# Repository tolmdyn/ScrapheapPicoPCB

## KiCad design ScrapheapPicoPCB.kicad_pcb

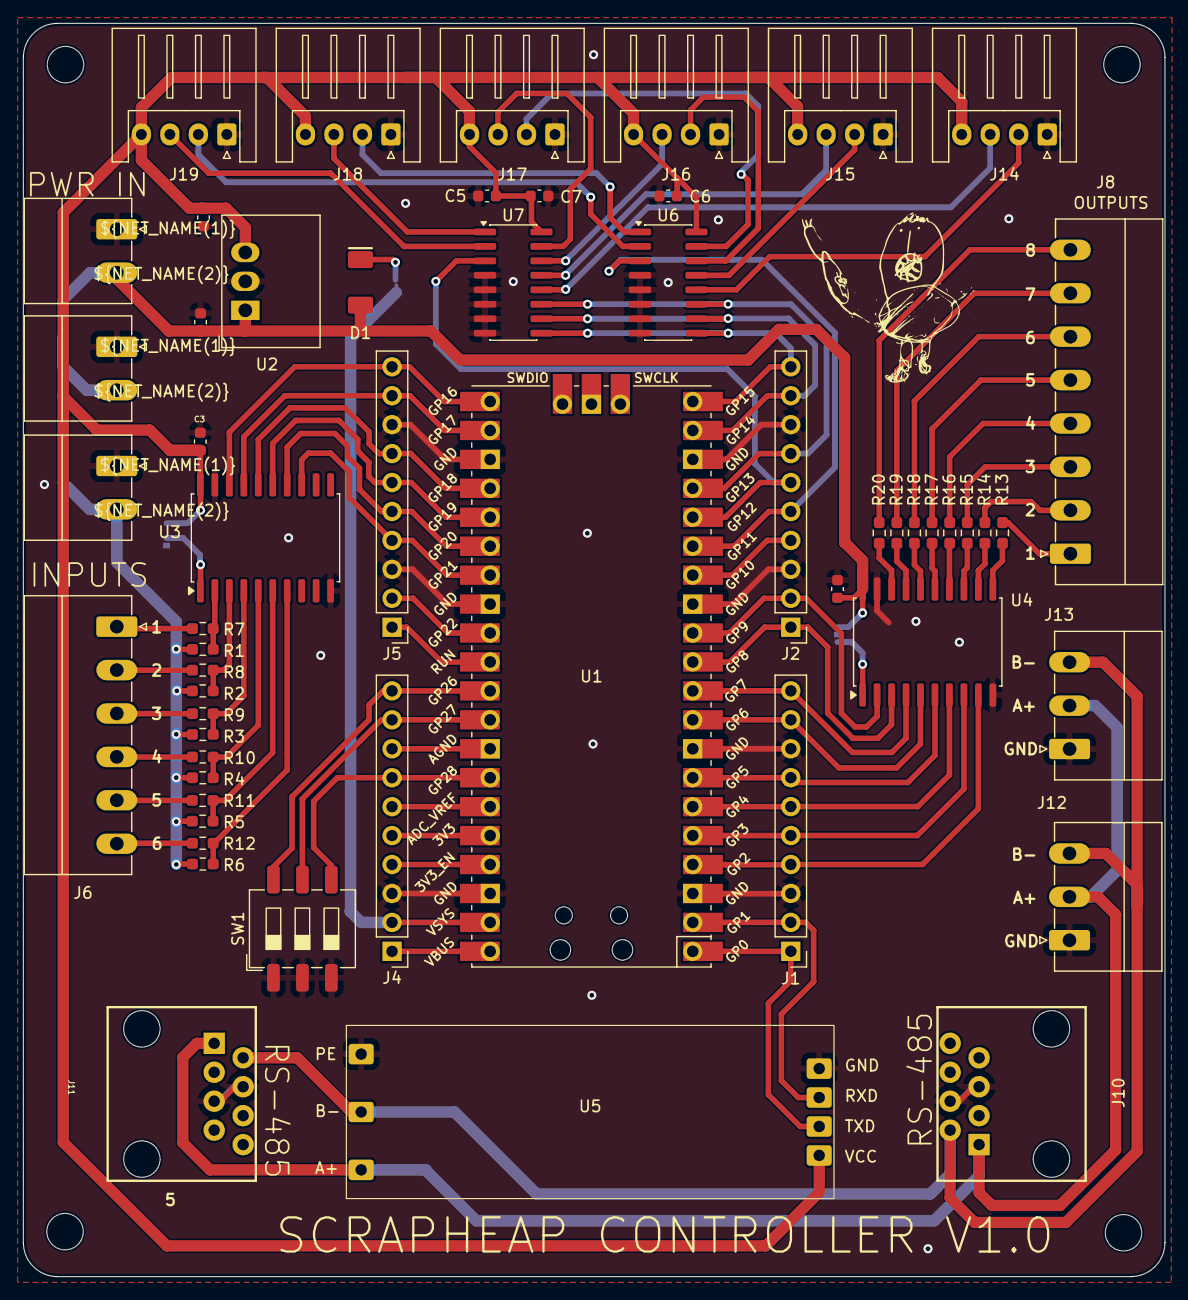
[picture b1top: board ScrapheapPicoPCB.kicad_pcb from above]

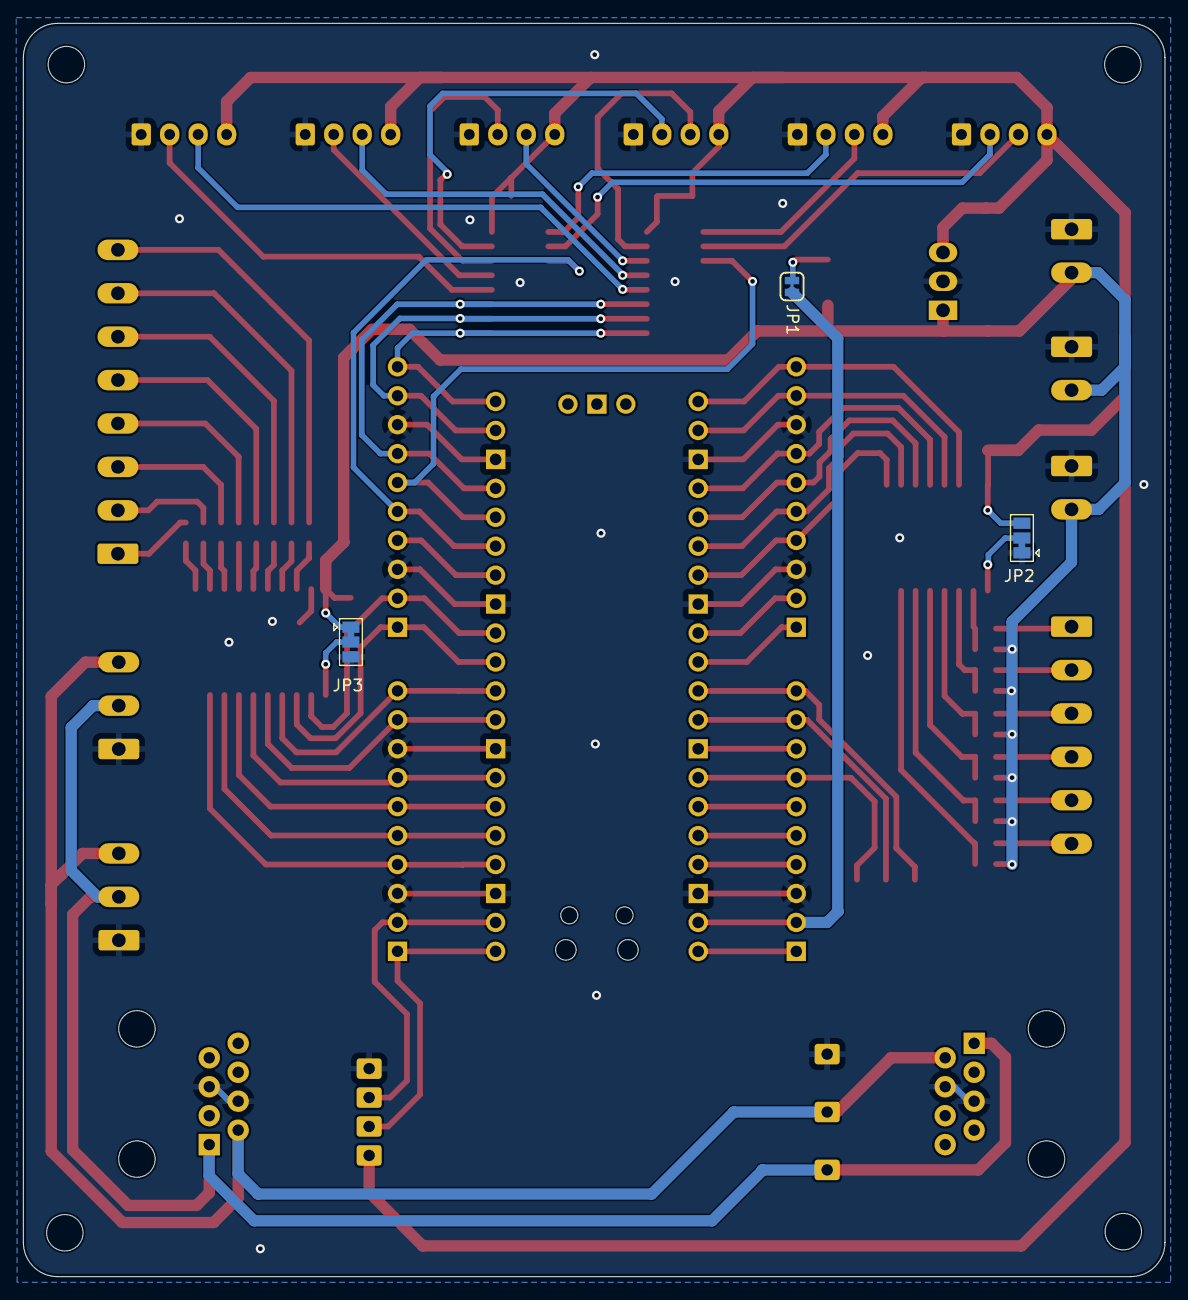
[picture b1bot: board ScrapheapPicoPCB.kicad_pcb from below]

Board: 2 copper layers, 100.2 x 110.0 mm, 62 parts (3 on the bottom side), 81 nets.

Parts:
C1, C2, C7: 10uF; C_0603_1608Metric
C3, C4, C5, C6: 0.1uF; C_0603_1608Metric
D1: SS14; SMA
H1, H2, H3, H4: MountingHole; MountingHole_3.2mm_M3
J1, J2, J4, J5: 1; PinHeader_1x10_P2.54mm_Vertical
J3: PWR_INPUT; PhoenixContact_MC_1,5_2-G-3.81_1x02_P3.81mm_Horizontal_Labe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
J6: SHIFTED_IN_CONN; PhoenixContact_MC_1,5_6-G-3.81_1x06_P3.81mm_Horizontal
J7: S_PWR1; PhoenixContact_MC_1,5_2-G-3.81_1x02_P3.81mm_Horizontal_Labe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
J8: SHIFTED_OUT_CONN; PhoenixContact_MC_1,5_8-G-3.81_1x08_P3.81mm_Horizontal
J9: S_PWR2; PhoenixContact_MC_1,5_2-G-3.81_1x02_P3.81mm_Horizontal_Labe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
J10: RJ45-IN; RJ45-8
J11: RJ45-OUT; RJ45-8
J12: RS485-IN; PhoenixContact_MC_1,5_3-G-3.81_1x03_P3.81mm_Horizontal
J13: RS485-OUT; PhoenixContact_MC_1,5_3-G-3.81_1x03_P3.81mm_Horizontal
J14: NFC_CONN_0; JST_XH_S4B-XH-A_1x04_P2.50mm_Horizontal
J15: NFC_CONN_1; JST_XH_S4B-XH-A_1x04_P2.50mm_Horizontal
J16: NFC_CONN_2; JST_XH_S4B-XH-A_1x04_P2.50mm_Horizontal
J17: NFC_CONN_3; JST_XH_S4B-XH-A_1x04_P2.50mm_Horizontal
J18: NFC_CONN_4; JST_XH_S4B-XH-A_1x04_P2.50mm_Horizontal
J19: NFC_CONN_5; JST_XH_S4B-XH-A_1x04_P2.50mm_Horizontal
JP1: SolderJumper_2_Bridged; Jumper_2_NC_Trace
JP2: IN_DIR; SolderJumper-3_P1.3mm_Bridged12_Pad1.0x1.5mm
JP3: OUT_DIR; SolderJumper-3_P1.3mm_Bridged12_Pad1.0x1.5mm
R1, R2, R3, R4, R5, R6: 4.7k; R_0603_1608Metric_Pad0.98x0.95mm_HandSolder
R7, R8, R9, R10, R11, R12, R13, R14, R15, R16, R17, R18, R19, R20: 100R; R_0603_1608Metric_Pad0.98x0.95mm_HandSolder
SW1: SW_DIP_x03; SW_DIP_SPSTx03_Slide_6.7x9.18mm_W8.61mm_P2.54mm_LowProfile
U1: Pico; RPi_Pico_SMD_TH
U2: R-78B3.3-2.0; Converter_DCDC_RECOM_R-78B-2.0_THT
U3: SN74LVC245APW; SOIC-20W_7.5x12.8mm_P1.27mm
U4: 74HCT245; SOIC-20W_7.5x12.8mm_P1.27mm
U5: RS485-TTL; Waveshare-RS485-TTL
U6, U7: 74HC4051; SOIC-16_3.9x9.9mm_P1.27mm

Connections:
3.3V: C2.1, C3.1, C5.1, C6.1, C7.1, J14.4, J15.4, J16.4, J17.4, J18.4, J19.4, JP2.3 (B), U2.3 (OUT), U3.20 (VCC), U5.7 (VCC), U6.16 (VCC), U7.16 (VCC)
3V3_EN: J4.4, U1.37 (3V3_EN)
3v3_OUT: J4.5, U1.36 (3V3)
5V: C1.1, C4.1, D1.2 (A), J3.2, J7.2, J9.2, JP3.1 (A), R1.2, R2.2, R3.2, R4.2, R5.2, R6.2, U2.1 (IN), U4.20 (VCC)
A: J10.1, J11.1, J12.2, J13.2, U5.1 (A+)
ADC_VREF: J4.6, U1.35 (ADC_VREF)
AGND: J4.8, U1.33 (AGND)
B: J10.2, J11.2, J12.3, J13.3, U5.2 (B-)
GND: C1.2, C2.2, C3.2, C4.2, C5.2, C6.2, C7.2, J1.3, J1.8, J2.3, J2.8, J3.1, J4.3, J5.3, J5.8, J7.1, J9.1, J10.4, J10.5, J11.4, J11.5, J12.1, J13.1, J14.1, J15.1, J16.1, J17.1, J18.1, J19.1, JP2.1 (A), JP3.3 (B), SW1.1, SW1.2, SW1.3, U1.3 (GND), U1.8 (GND), U1.13 (GND), U1.18 (GND), U1.23 (GND), U1.28 (GND), U1.38 (GND), U2.2 (GND), U3.10 (GND), U3.19 (~OE), U4.10 (GND), U4.19 (CE), U5.3 (PE), U5.4 (GND), U6.4 (A7), U6.5 (A5), U6.6 (~E), U6.7 (VEE), U6.8 (GND), U7.4 (A7), U7.5 (A5), U7.6 (~E), U7.7 (VEE), U7.8 (GND)
GPIO0: J1.1, U1.1 (GPIO0), U5.6 (TXD)
GPIO1: J1.2, U1.2 (GPIO1), U5.5 (RXD)
GPIO2: J1.4, U1.4 (GPIO2), U4.9 (A7)
GPIO3: J1.5, U1.5 (GPIO3), U4.8 (A6)
GPIO4: J1.6, U1.6 (GPIO4), U4.7 (A5)
GPIO5: J1.7, U1.7 (GPIO5), U4.6 (A4)
GPIO6: J1.9, U1.9 (GPIO6), U4.5 (A3)
GPIO7: J1.10, U1.10 (GPIO7), U4.4 (A2)
GPIO8: J2.1, U1.11 (GPIO8), U4.3 (A1)
GPIO9: J2.2, U1.12 (GPIO9), U4.2 (A0)
GPIO10: J2.4, U1.14 (GPIO10)
GPIO11: J2.5, U1.15 (GPIO11), U6.3 (A)
GPIO12: J2.6, U1.16 (GPIO12), U7.3 (A)
GPIO13: J2.7, U1.17 (GPIO13), U6.11 (S0), U7.11 (S0)
GPIO14: J2.9, U1.19 (GPIO14), U6.10 (S1), U7.10 (S1)
GPIO15: J2.10, U1.20 (GPIO15), U6.9 (S2), U7.9 (S2)
GPIO16: J5.10, U1.21 (GPIO16), U3.18 (B1)
GPIO17: J5.9, U1.22 (GPIO17), U3.17 (B2)
GPIO18: J5.7, U1.24 (GPIO18), U3.16 (B3)
GPIO19: J5.6, U1.25 (GPIO19), U3.15 (B4)
GPIO20: J5.5, U1.26 (GPIO20), U3.14 (B5)
GPIO21: J5.4, U1.27 (GPIO21), U3.13 (B6)
GPIO22: J5.2, U1.29 (GPIO22)
GPIO26_ADC0: J4.10, SW1.6, U1.31 (GPIO26_ADC0)
GPIO27_ADC1: J4.9, SW1.5, U1.32 (GPIO27_ADC1)
GPIO28_ADC2: J4.7, SW1.4, U1.34 (GPIO28_ADC2)
IN0: R1.1, R7.2, U3.2 (A1)
IN1: R2.1, R8.2, U3.3 (A2)
IN2: R3.1, R9.2, U3.4 (A3)
IN3: R4.1, R10.2, U3.5 (A4)
IN4: R5.1, R11.2, U3.6 (A5)
IN5: R6.1, R12.2, U3.7 (A6)
NFC_RX_0: J14.3, U7.12 (A3)
NFC_RX_1: J15.3, U7.13 (A0)
NFC_RX_2: J16.3, U7.14 (A1)
NFC_RX_3: J17.3, U7.15 (A2)
NFC_RX_4: J18.3, U7.1 (A4)
NFC_RX_5: J19.3, U7.2 (A6)
NFC_TX_0: J14.2, U6.12 (A3)
NFC_TX_1: J15.2, U6.13 (A0)
NFC_TX_2: J16.2, U6.14 (A1)
NFC_TX_3: J17.2, U6.15 (A2)
NFC_TX_4: J18.2, U6.1 (A4)
NFC_TX_5: J19.2, U6.2 (A6)
unnamed: D1.1 (K), JP1.2 (B)
unnamed: J6.1, R7.1
unnamed: J6.2, R8.1
unnamed: J6.3, R9.1
unnamed: J6.4, R10.1
unnamed: J6.5, R11.1
unnamed: J6.6, R12.1
unnamed: J8.1, R13.2
unnamed: J8.2, R14.2
unnamed: J8.3, R15.2
unnamed: J8.4, R16.2
unnamed: J8.5, R17.2
unnamed: J8.6, R18.2
unnamed: J8.7, R19.2
unnamed: J8.8, R20.2
unnamed: JP2.2 (C), U3.1 (DIR)
unnamed: JP3.2 (C), U4.1 (A->B)
OUT0: R13.1, U4.11 (B7)
OUT1: R14.1, U4.12 (B6)
OUT2: R15.1, U4.13 (B5)
OUT3: R16.1, U4.14 (B4)
OUT4: R17.1, U4.15 (B3)
OUT5: R18.1, U4.16 (B2)
OUT6: R19.1, U4.17 (B1)
OUT7: R20.1, U4.18 (B0)
RUN: J5.1, U1.30 (RUN)
VBUS: J4.1, U1.40 (VBUS)
VSYS: J4.2, JP1.1 (A), U1.39 (VSYS)
